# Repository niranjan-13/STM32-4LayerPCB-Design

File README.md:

# STM32-4LayerPCB-Design
Designed STM32 4-layered PCB based on STM32F405 Microcontroller in KiCAD software

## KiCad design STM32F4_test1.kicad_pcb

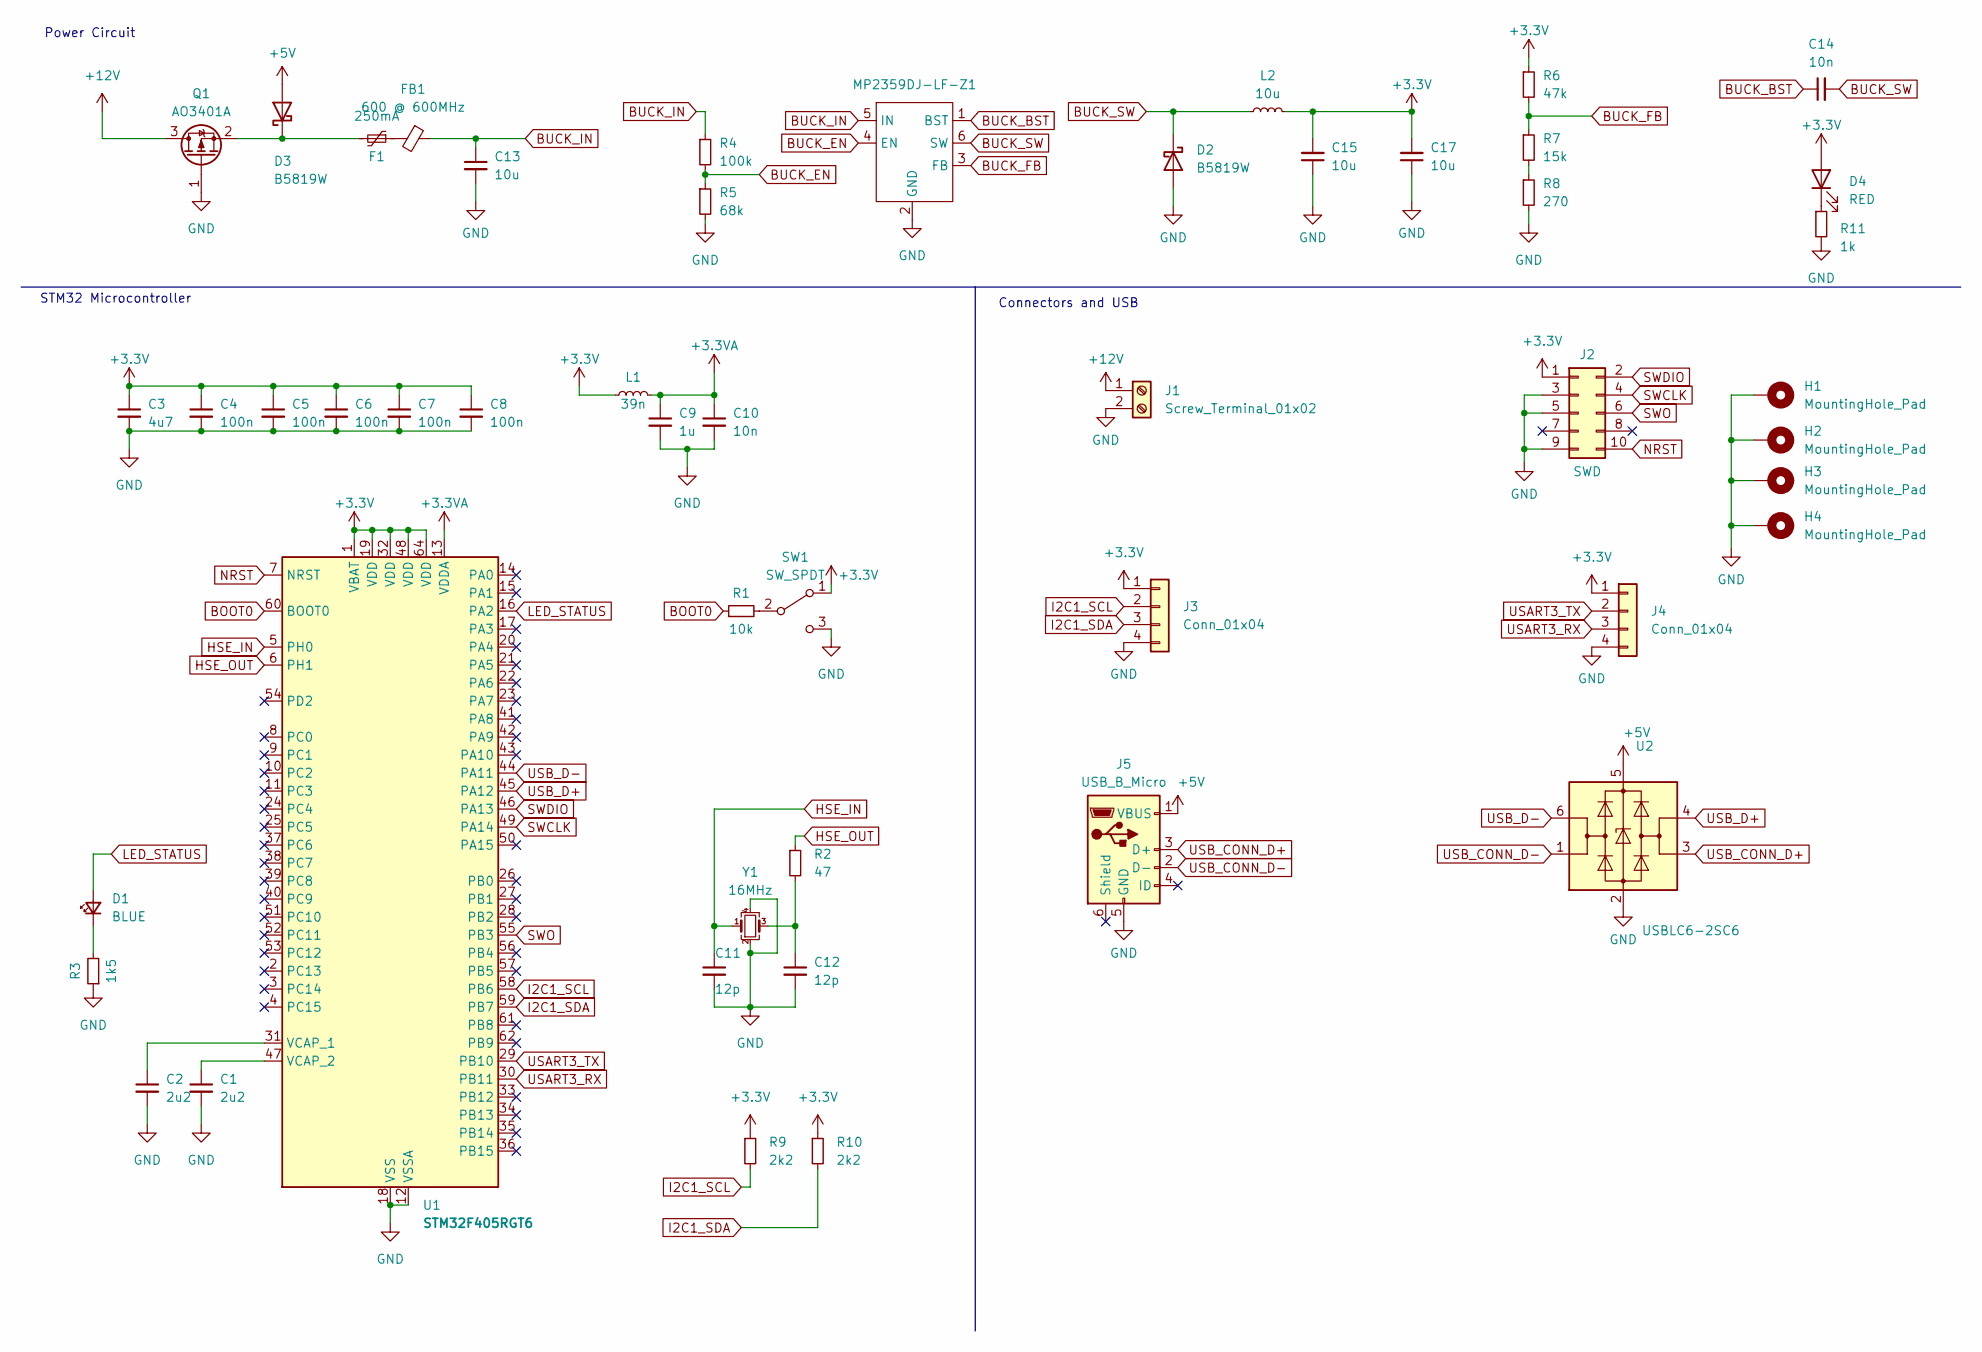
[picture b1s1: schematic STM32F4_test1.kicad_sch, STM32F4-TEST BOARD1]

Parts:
C1, C2: 2u2; C_0603_1608Metric
C3: 4u7; C_0603_1608Metric
C4, C5, C6, C7, C8: 100n; C_0402_1005Metric
C9: 1u; C_0402_1005Metric
C10: 10n; C_0402_1005Metric
C11, C12: 12p; C_0402_1005Metric
C13, C15, C17: 10u; C_1206_3216Metric
C14: 10n; C_0603_1608Metric
D1: BLUE; LED_0603_1608Metric
D2, D3: B5819W; D_SOD-123
D4: RED; LED_0603_1608Metric
F1: 250mA; Fuse_1206_3216Metric
FB1: 600 @ 600MHz; L_0805_2012Metric
H1, H2, H3, H4: MountingHole_Pad; MountingHole_4.3mm_M4_Pad_Via
J1: Screw_Terminal_01x02; TerminalBlock_Phoenix_PT-1,5-2-3.5-H_1x02_P3.50mm_Horizontal
J2: SWD; PinHeader_2x05_P1.27mm_Vertical_SMD
J3, J4: Conn_01x04; Molex_PicoBlade_53048-0410_1x04_P1.25mm_Horizontal
J5: USB_B_Micro; USB_Micro-B_GCT_USB3076-30-A
L1: 39n; L_0402_1005Metric
L2: 10u; L_TracoPower_TCK-047_5.2x5.8mm
MP2359DJ-LF-Z1: SOT-23-6
Q1: AO3401A; SOT-23
R1: 10k; R_0402_1005Metric
R2: 47; R_0402_1005Metric
R3: 1k5; R_0603_1608Metric
R4: 100k; R_0603_1608Metric
R5: 68k; R_0603_1608Metric
R6: 47k; R_0603_1608Metric
R7: 15k; R_0603_1608Metric
R8: 270; R_0603_1608Metric
R9, R10: 2k2; R_0402_1005Metric
R11: 1k; R_0603_1608Metric
SW1: SW_SPDT; SW_SPDT_PCM12
U1: STM32F405RGT6; LQFP-64_10x10mm_P0.5mm
U2: USBLC6-2SC6; SOT-23-6
Y1: 16MHz; Crystal_SMD_3225-4Pin_3.2x2.5mm

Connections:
+3.3V: C3.1, C4.1, C5.1, C6.1, C7.1, C8.1, C15.2, C17.2, D4.2 (A), J2.1, J3.1, J4.1, L1.1, L2.2, R6.1, R9.1, R10.1, SW1.1 (A), U1.1 (VBAT), U1.19 (VDD), U1.32 (VDD), U1.48 (VDD), U1.64 (VDD)
+3.3VA: C9.1, C10.1, L1.2, U1.13 (VDDA)
+5V: D3.2 (A), J5.1 (VBUS), U2.5 (VBUS)
+12V: J1.1, Q1.3 (D)
BOOT0: R1.1, U1.60 (BOOT0)
BUCK_BST: C14.1, MP2359DJ-LF-Z1.1 (BST)
BUCK_EN: MP2359DJ-LF-Z1.4 (EN), R4.2, R5.1
BUCK_FB: MP2359DJ-LF-Z1.3 (FB), R6.2, R7.1
BUCK_IN: C13.1, FB1.1, MP2359DJ-LF-Z1.5 (IN), R4.1
BUCK_SW: C14.2, D2.1 (K), L2.1, MP2359DJ-LF-Z1.6 (SW)
GND: C1.2, C2.2, C3.2, C4.2, C5.2, C6.2, C7.2, C8.2, C9.2, C10.2, C11.2, C12.2, C13.2, C15.1, C17.1, D2.2 (A), H1.1, H2.1, H3.1, H4.1, J1.2, J2.3, J2.5, J2.9, J3.4, J4.4, J5.5 (GND), MP2359DJ-LF-Z1.2 (GND), Q1.1 (G), R3.1, R5.2, R8.2, R11.2, SW1.3 (C), U1.12 (VSSA), U1.18 (VSS), U1.63 (VSS), U2.2 (GND), Y1.2, Y1.4
HSE_IN: C11.1, U1.5 (PH0), Y1.1
HSE_OUT: R2.1, U1.6 (PH1)
I2C1_SCL: J3.2, R9.2, U1.58 (PB6)
I2C1_SDA: J3.3, R10.2, U1.59 (PB7)
LED_STATUS: D1.2 (A), U1.16 (PA2)
NRST: J2.10, U1.7 (NRST)
unnamed: C12.1, R2.2, Y1.3
unnamed: D1.1 (K), R3.2
unnamed: D3.1 (K), F1.2, Q1.2 (S)
unnamed: D4.1 (K), R11.1
unnamed: F1.1, FB1.2
unnamed: R7.2, R8.1
unnamed: R1.2, SW1.2 (B)
unnamed: C2.1, U1.31 (VCAP_1)
unnamed: C1.1, U1.47 (VCAP_2)
SWCLK: J2.4, U1.49 (PA14)
SWDIO: J2.2, U1.46 (PA13)
SWO: J2.6, U1.55 (PB3)
USART3_RX: J4.3, U1.30 (PB11)
USART3_TX: J4.2, U1.29 (PB10)
USB_CONN_D+: J5.3 (D+), U2.3 (I/O2)
USB_CONN_D-: J5.2 (D-), U2.1 (I/O1)
USB_D+: U1.45 (PA12), U2.4 (I/O2)
USB_D-: U1.44 (PA11), U2.6 (I/O1)

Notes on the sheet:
Power Circuit
STM32 Microcontroller
Connectors and USB

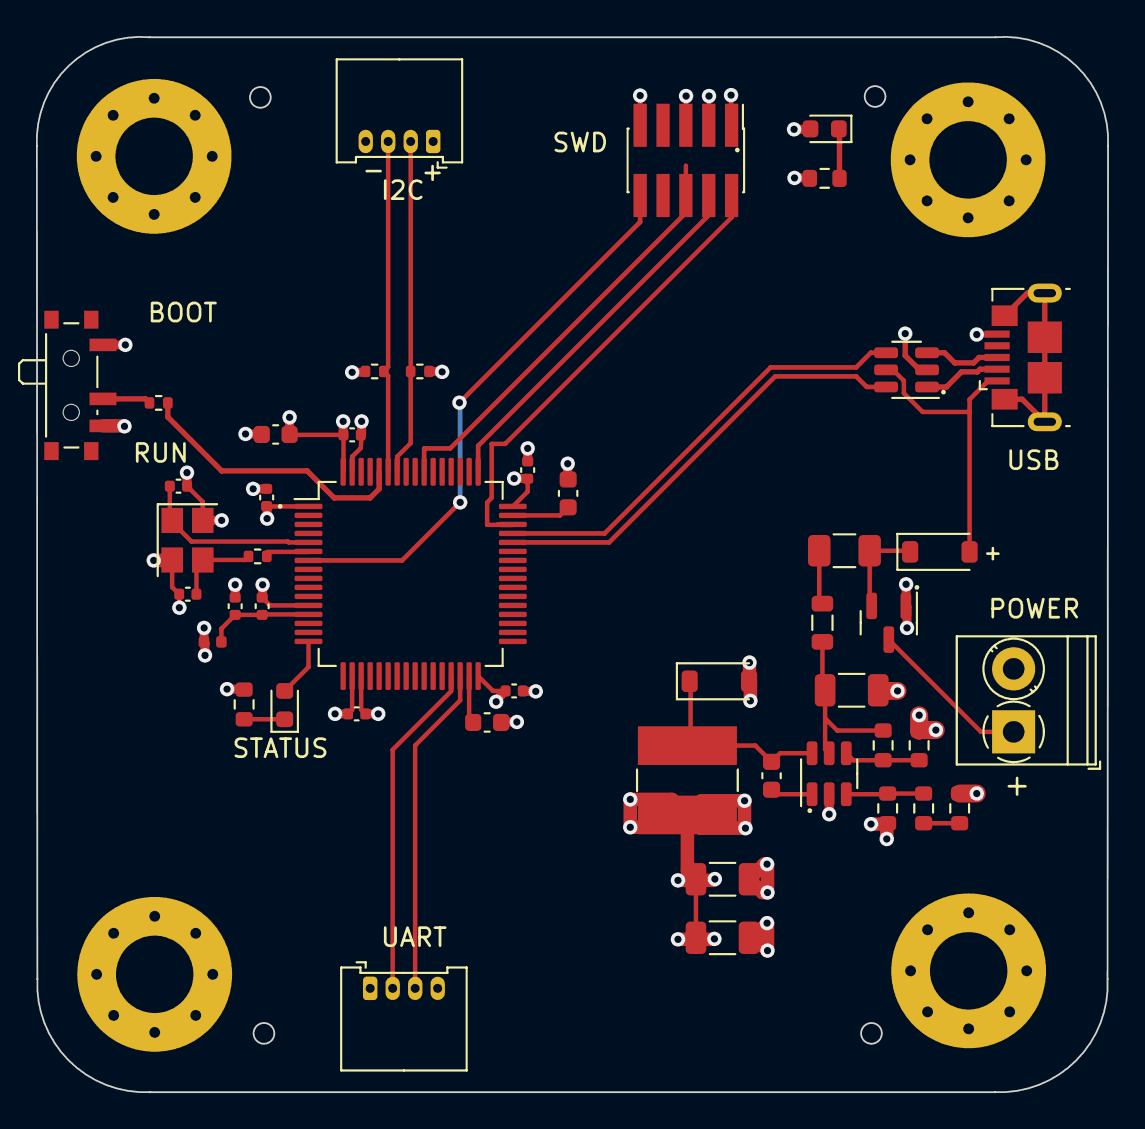
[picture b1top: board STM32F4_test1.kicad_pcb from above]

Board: 4 copper layers, 59.5 x 58.6 mm, 50 parts (0 on the bottom side), 35 nets.

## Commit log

2023-08-01 pcb files of stm32f4
2023-08-01 added images
